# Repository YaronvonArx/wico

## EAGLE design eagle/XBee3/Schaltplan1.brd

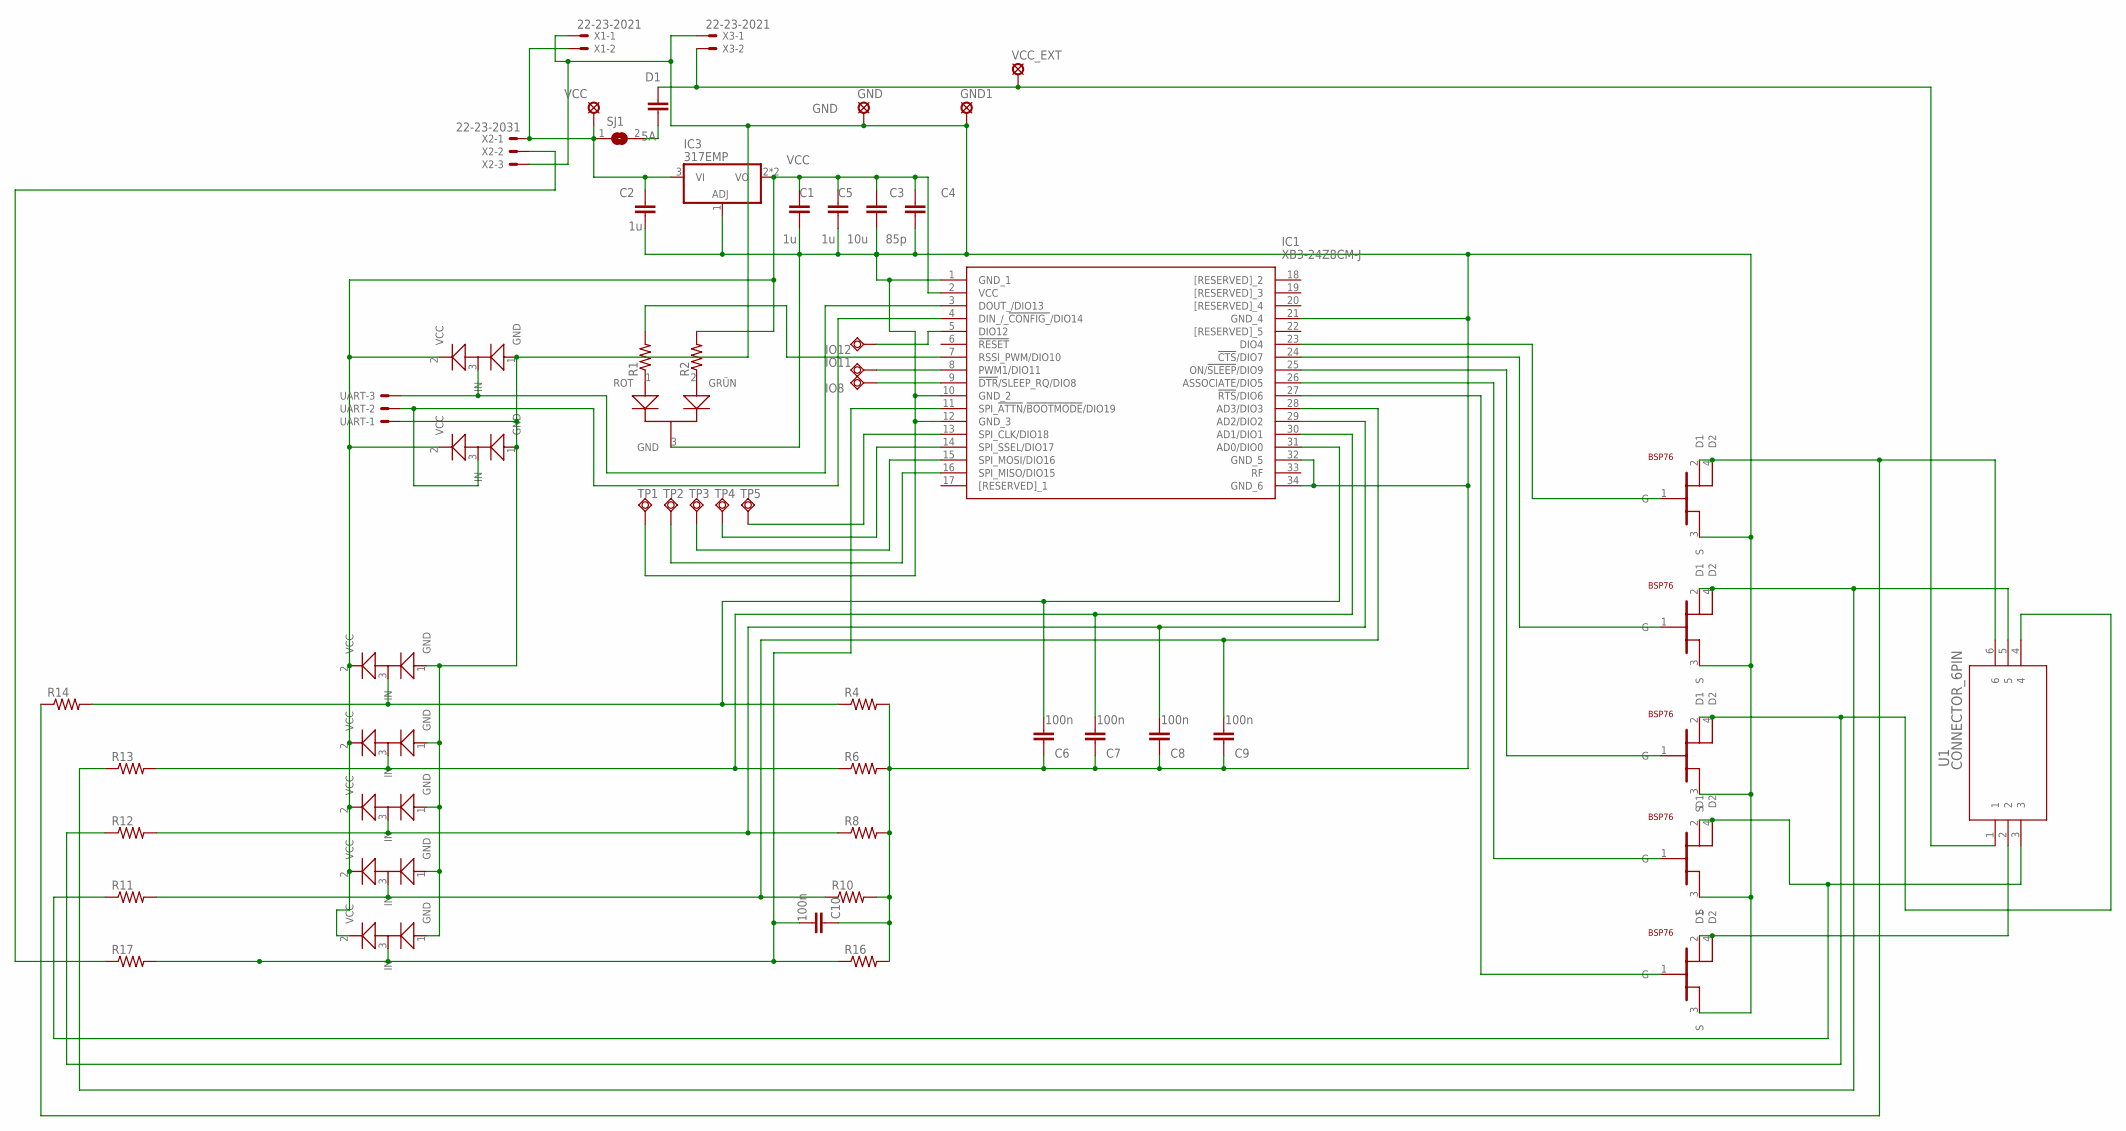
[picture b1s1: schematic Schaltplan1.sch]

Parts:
C1, C2, C5: 1u; CAP_0805
C3: 10u; CAP_0805
C4: 85p; CAP_0805
C6, C7, C8, C9, C10: 100n; CAP_0805
D1: 5A; CAP_0805
GND, GND1: LSP10
IC1: XB3-24Z8CM-J; XB324Z8CMJ
IC3: 317EMP; SOT223
IO8, IO11, IO12: TPSQB1,27; B1,27
LED: LED_RG_SOT23; SOT23
R1: 150; RES_0805
R2, R6, R8, R10, R11, R12, R13, R14, R16, R17: CRCW08050000Z0EA; RES_0805
R4: 47k; RES_0805
SJ1: SJW
TP1, TP2, TP3, TP4, TP5: TPSQB1,27; B1,27
U1: CONNECTOR_6PIN; 282836-6
U$1, U$2, U$3, U$4, U$5: BSP76; SOT223
U$6, U$7, U$8, U$9, U$10, U$11, U$12: TVS-DIODE; SOT23-R
UART: 22-23-2031
VCC: LSP10
VCC_EXT: LSP10
X1, X3: 22-23-2021
X2: 22-23-2031

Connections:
GND: C1.2, C2.2, C3.1, C4.1, C5.2, C6.1, C7.1, C8.1, C9.1, C10.1, GND.MP, GND1.MP, IC1.1 (GND_1), IC1.10 (GND_2), IC1.12 (GND_3), IC1.21 (GND_4), IC1.32 (GND_5), IC1.34 (GND_6), IC3.1 (ADJ), LED.3 (GND), R4.2, R6.2, R8.2, R10.2, R16.2, TP1.TP, U$1.3 (S), U$2.3 (S), U$3.3 (S), U$4.3 (S), U$5.3 (S), U$6.1 (GND), U$7.1 (GND), U$8.1 (GND), U$9.1 (GND), U$10.1 (GND), U$11.1 (GND), U$12.1 (GND), UART.1, X1.1, X2.3, X3.1
unnamed: C2.1, IC3.3 (VI), SJ1.1, VCC.MP, X1.2, X2.1
unnamed: IC1.5 (DIO12), IO12.TP
unnamed: IC1.27 (!RTS!/DIO6), U$5.1 (G)
unnamed: IC1.26 (ASSOCIATE/DIO5), U$4.1 (G)
unnamed: IC1.25 (ON/!SLEEP!/DIO9), U$3.1 (G)
unnamed: IC1.24 (!CTS!/DIO7), U$2.1 (G)
unnamed: IC1.23 (DIO4), U$1.1 (G)
unnamed: U1.2, U$5.2 (D1), U$5.4 (D2)
unnamed: R14.1, U1.6, U$1.2 (D1), U$1.4 (D2)
unnamed: IC1.3 (DOUT_/DIO13), U$11.3 (IN), UART.3
unnamed: D1.1, U1.1, VCC_EXT.MP, X3.2
unnamed: C6.2, IC1.31 (AD0/DIO0), R4.1, R14.2, U$7.3 (IN)
unnamed: C7.2, IC1.30 (AD1/DIO1), R6.1, R13.2, U$8.3 (IN)
unnamed: C8.2, IC1.29 (AD2/DIO2), R8.1, R12.2, U$9.3 (IN)
unnamed: C9.2, IC1.28 (AD3/DIO3), R10.1, R11.2, U$10.3 (IN)
unnamed: IC1.14 (SPI_SSEL/DIO17), TP4.TP
unnamed: IC1.4 (DIN_/_!CONFIG_!/DIO14), U$12.3 (IN), UART.2
unnamed: D1.2, SJ1.2
unnamed: LED.1 (ROT), R1.1
unnamed: LED.2 (GRÜN), R2.1
unnamed: IC1.7 (RSSI_PWM/DIO10), R1.2
unnamed: IC1.13 (SPI_CLK/DIO18), TP5.TP
unnamed: R13.1, U1.5, U$2.2 (D1), U$2.4 (D2)
unnamed: IC1.16 (SPI_MISO/DIO15), TP2.TP
unnamed: IC1.15 (SPI_MOSI/DIO16), TP3.TP
unnamed: R12.1, U1.4, U$3.2 (D1), U$3.4 (D2)
unnamed: C10.2, IC1.11 (SPI_!ATTN!/!BOOTMODE!/DIO19), R16.1, R17.2, U$6.3 (IN)
unnamed: IC1.8 (PWM1/DIO11), IO11.TP
unnamed: IC1.9 (!DTR!/SLEEP_RQ/DIO8), IO8.TP
unnamed: R11.1, U1.3, U$4.2 (D1), U$4.4 (D2)
unnamed: R17.1, X2.2
VCC: C1.1, C3.2, C4.2, C5.1, IC1.2 (VCC), IC3.2 (VO), IC3.4 (VO), R2.2, U$6.2 (VCC), U$7.2 (VCC), U$8.2 (VCC), U$9.2 (VCC), U$10.2 (VCC), U$11.2 (VCC), U$12.2 (VCC)

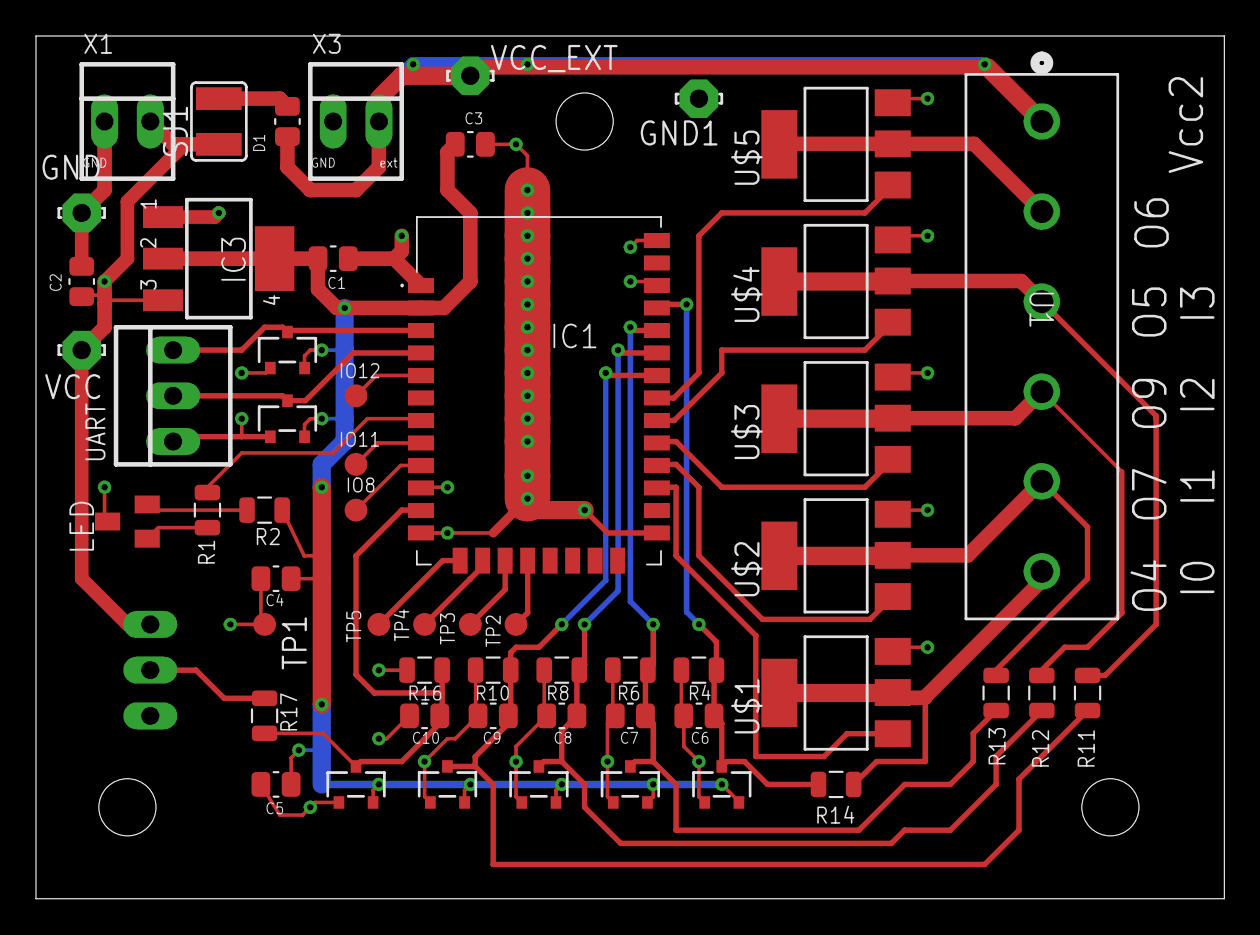
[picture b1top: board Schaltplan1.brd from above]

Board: 2 copper layers, 66.0 x 47.9 mm, 56 parts (1 on the bottom side), 33 nets.

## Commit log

2019-06-20 first try
2019-06-20 erster Erfolg
2019-06-20 Erster App upload
2019-06-27 Erweitert auf 10 Kanäle, Hostswitch(Schule, Zuhause), Serialswitch(PC, Raspi)
2019-06-28 Config Datei
2019-06-28 CSV durch ConfigParser ersetzt, 1. Programm Ableuf Funktion
2019-06-28 Programmfunktion implementiert
2019-07-07 Board für das XBee Modul
2019-07-07 Board rev0.2
2019-07-09 Placement grundsätzlich fertig
2019-07-27 Mit ADC Sampling und Schliessen Button
2019-07-27 Fertiges Board Vers. Juli 19 (Bestellt)
2019-07-28 IP Eingabefeld und Programm start Button
2019-07-28 Vibrator hinzugefügt
2019-07-28 Vibrator auch zu ProgrammButton hinzugefügt
2019-07-28 Programm Modus update und Programm über App startbar
2019-07-28 kleines Update
2019-07-28 App update IP Addresse nun wirklich wählbar
